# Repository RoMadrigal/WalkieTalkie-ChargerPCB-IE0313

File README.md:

# WalkieTalkie-ChargerPCB-IE0313

Repositorio para la tarea del curso IE0313 sobre el diseño de una PCB de una fuente de alimentación para un Walkie-Talkie. Contiene el circuito esquemático, el diseño de la PCB en KiCad y documentación sobre los componentes a utilizar, el procedimiento de diseño y otros detalles. 

Este repositorio y sus contenidos fueron diseñados durante el curso IE0313 durante el periodo II-2024 por los siguientes integrantes del equipo:

<div align="center">

|        **Integrantes**      | **Carné** | **Correo electrónico**|
|:---------------------------:|:---------:|:---------------------:|
|    Anthony Calvo García     |   C11433  |  anthonycalvo50@gmail.com |
|   Rodrigo Madrigal Montes   |   C24458  | rmadrigalmontes@gmail.com |

</div>

## Agradecimientos a PCBWay

Queremos expresar nuestros agradecimientos a **PCBWay** por su increíble apoyo en la fabricación de las PCBs para esta tarea. Desde el primer contacto hasta la recepción de las placas, la experiencia fue excelente. Las PCBs que recibimos superaron nuestras expectativas en términos de precisión y acabado. Cada detalle fue manejado con cuidado, asegurando un rendimiento óptimo y mostrando una calidad sobresaliente.

La comunicación fue clara y fluida, y el tiempo de entrega se cumplió en el plazo esperado. Recibimos las placas en perfectas condiciones, en un empaque seguro y listas para ensamblar. Además siempre estuvieron disponibles para responder preguntas y asegurarse de que todo saliera según lo planeado, lo cual nos brindó seguridad y apoyo durante todo el proceso de pedido.

### Resultado del ensamblaje

Soldar y ensamblar estas placas fue una experiencia cómoda y bastante agradable, ya que todas las medidas de las huellas que se escogieron para los componentes en la fase de diseño corresponden perfectamente en el producto terminado y los resultados finales son un testimonio del compromiso de **PCBWay** con la excelencia. Aquí se muestran fotografías de la PCB ensamblada y terminada:

|  |
|:--:|
| *Vista frontal de la PCB sin ensamblar* |

|  |
|:--:|
| *Vista trasera de la PCB sin ensamblar* |

Como se ve las placas se corresponden con lo esperado, y una vez se soldaron los componentes el resultado es el siguiente:

|  |
|:--:|
| *Vista frontal de la PCB ensamblada* |

|  |
|:--:|
| *Vista isométrica de la PCB ensamblada* |

|  |
|:--:|
|  |

Recomendamos sus servicios para cualquiera que busque fabricar PCBs con precisión y profesionalismo, visitando su sitio web en [pcbway.com](https://www.pcbway.com).

## Organización y contenido de los directorios 

Este repositorio contiene dos directorios principales, cuyos contenidos son:

- `kicad_project`: Contiene los archivos de diseño y configuarción del proyecto
    - `CargadorWalkieTalkie.kicad_pcb`
    - `CargadorWalkieTalkie.kicad_pro`
    - `CargadorWalkieTalkie.kicad_sch`

- `outputs`: Contiene todos los archivos de salida de *KiCad*

Si se desea utilizar este diseño y manufacturarlo por medio de un fabricante se debe comprimir los archivos incluidos en la carpeta `outputs` en un archivo `.zip` y este se puede cargar en la página del fabricante para ordenar la fabricación de la PCB. 

## Circuito base

El circuito del que partimos para diseñar la PCB es el que se diseñó en la **Tarea 3**:

<div align="center">

|  |
|:--:|
| *Circuto de la fuente de alimentación* |

</div>

Para este ciruito se tiene el siguiente listado de componentes:

<div align="center">

|     Componente     | Especificación |
|:------------------:|:--------------:|
|    Transformador   |      20:1      |
| Diodo rectificador |     1N4007     |
|      Capacitor     |     1.1 mF     |
|     Resistencia    |      6 Ω       |
|     Diodo Zener    |     1N5338B    |
|      Fusible 1     |     400 mA     |
|      Fusible 2     |     200 mA     |

</div>

## Diseño del esquemático 

Primero para el diseño del esquemático de la PCB se seleccionó la opción *Schematic Editor* en *KiCad*, posteriormente se siguió la metodología de pasos descrita en la página de [Arcos-Lab Wiki](https://wiki.arcoslab.org/en/tutorials/kicad/example), a lo cual primero se definieron el el título, fecha y revisión del proyecto. 

Posteriormente se procedió a agregar los símbolos de cada componente a utilizar en el esquemático, acomodarlos y realizar las conexiones, a lo cual se obtuvo lo siguiente:

<div align="center">

|  |
|:--:|
| *Diseño del esquemático* |

</div>

Aquí hay algunas elecciones que es importante mencionar son:

### Transformador

Se realizó una investigación sobre diseños de circuitos en el mismo programa que eran similares a este y se encontró que en base a las recomendaciones y experiencias de estos usuarios determinamos que era mejor dejar el transformador fuera de la PCB ya que consumen mucho más espacio y es más seguro conectarlo como un componente externo, por lo cual para este diseño consideramos que la salida del transformador se conecta en la terminal `J1`. 

### Elección de huellas y componentes

Por otro lado en cuanto a las huellas de los componentes por ejemplo para los diodos, tanto para los `1n4007` y el `1n5338B` se utilizo la huella que ya venía asignada por defecto en el programa; y aplicamos lo mismo para la resistencia y las terminales. Ahora bien en cuanto al capacitor se realizó la busqueda de varios capacitores disponibles en el mercado para poder determinar las dimensiones a utilizar del mismo. 

Nos terminamos decantando por los modelos de capacitor del fabricante **Vishay** de una capacitancia de 1200 μF que es lo más cercano al valor teórico que definimos en el circuito. Y se utilizaron las medidas presentes en el [Datasheet 135D, 135J, 135L](https://www.vishay.com/docs/40024/135d-135j-135l.pdf) y se asignaron a la huella en el esquemático. Y además se agregó el *Datasheet* del mismo en la tabla de componentes en el programa para poder acceder rápidamente al mismo sin necesidad de salir del programa y buscarlo. 

Después se procedió a colocar las etiquetas a los nodos `Vs` y `gnd` para los nodos de alimentación y tierra, y se colocaron los símbolos de `PWR_FLAG` para indicar a *KiCad* que es por medio de estos nodos que se alimentará el circuito. 

Y una vez realizados todos los pasos anteriores se procedió a seleccionar la opción *Perform electrical rules check* para verificar que no haya conexiones inválidas o algún error en alguna configuración del circuito a lo cual obtuvimos una salida sin errores. 

## Diseño de la PCB

Primero se realizó la configuración previa en el editor de PCB, donde definimos que la placa tendría dos capas y se definieron el el título, fecha y revisión del proyecto en esta página. Posteriormente se utilizó la opción *Update PCB with schematic changes* para poder importar los modelos del esquemático a la página del editor de PCB.

Luego de esto se procedió a acomodar los componente en el editor tomando en cuenta la configuarción que menos espacio requiera y sea fácil de reconocer cada componente. Se realizaron las conexiones de los componentes, entre las capas **F. Cu** y **B. Cu** y se asignó que en la capa **F. Cu** se conectaría el nodo `gnd` y la capa **B. Cu** va ligada a `Vs`. Por último se procedió a hacer el relleno de cada capa dentro del recuadro definido de la PCB que definimos y se corrieron las pruebas dentro del programa para asegurar que no haya errores, a lo cual se obtuvieron los siguientes resultados:

<div align="center">

|  |
|:--:|
| *Vista de la PCB con ambas capas superpuestas* |

</div>

Y viendo las conexiones de cada capa por separado se tiene los siguiente:

<div align="center">

|  |
|:--:|
| *Capa **F. Cu** de la PCB* |

</div>

<div align="center">

|  |
|:--:|
| *Capa **B. Cu** de la PCB* |

</div>

### Consideraciones adicionales

Por cuestiones de tiempo por el momento para este diseño no se tomó en cuenta la configuración del tamaño de las pistas de conexión en la PCB, pero esto queda pendiente como una futura mejora para el adecuado funcionamiento y como protección del circuito. Además tampoco tomamos en cuenta los fusibles en la placa por el mismo motivo y queda igualmente pendiente como mejora al diseño. 

Antes de terminar el diseño agregamos los nombre de los integrantes y de la placa (`WT-Charger V1`) en la parte trasera de la PCB haciendo uso de la capa **B. Silkscreen**, que como observación importante notamos que todo lo que se agregue en esta capa ya sea texto o un logo desde el editor debe verse en espejo ya que el editor mira la placa desde el frente de la misma. Agregando este cambio se consiguió lo siguente:

<div align="center">

|  |
|:--:|
| *Nombre de la placa y los integrantes en la parte trasera de la PCB* |

</div>

## Resultados finales

Como muestra de los resultados finales de este diseño se utilzó el visor 3D de *KiCad* para poder visualizar mejor la PCB, a lo cual se muestran los resultados finales en las siguientes imágenes:

<div align="center">

|  |
|:--:|
| *Vista frontal de la PCB* |

</div>

<div align="center">

|  |
|:--:|
| *Vista trasera de la PCB* |

</div>

<div align="center">

|  |
|:--:|
| *Vista isométrica de la PCB* |

</div>

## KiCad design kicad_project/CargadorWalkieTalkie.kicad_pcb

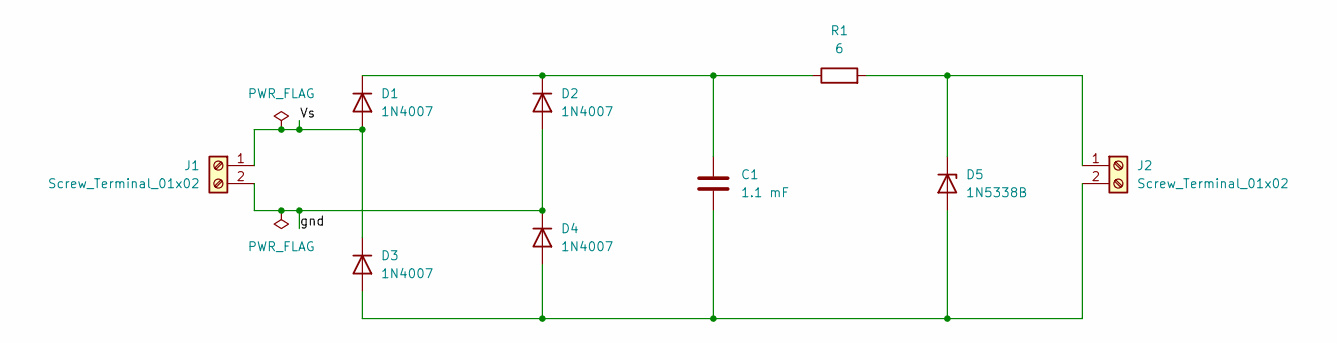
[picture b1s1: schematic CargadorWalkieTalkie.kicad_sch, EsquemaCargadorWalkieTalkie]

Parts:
C1: 1.1 mF; CP_Axial_L18.0mm_D6.5mm_P25.00mm_Horizontal
D1, D2, D3, D4: 1N4007; D_DO-41_SOD81_P10.16mm_Horizontal
D5: 1N5338B; D_DO-201_P15.24mm_Horizontal
J1, J2: Screw_Terminal_01x02; TerminalBlock_bornier-2_P5.08mm
R1: 6; R_Axial_DIN0204_L3.6mm_D1.6mm_P5.08mm_Horizontal

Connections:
/Vs: D1.2 (A), D3.1 (K), J1.1
/gnd: D2.2 (A), D4.1 (K), J1.2
unnamed: C1.1, D1.1 (K), D2.1 (K), R1.1
unnamed: C1.2, D3.2 (A), D4.2 (A), D5.2 (A), J2.2
unnamed: D5.1 (K), J2.1, R1.2

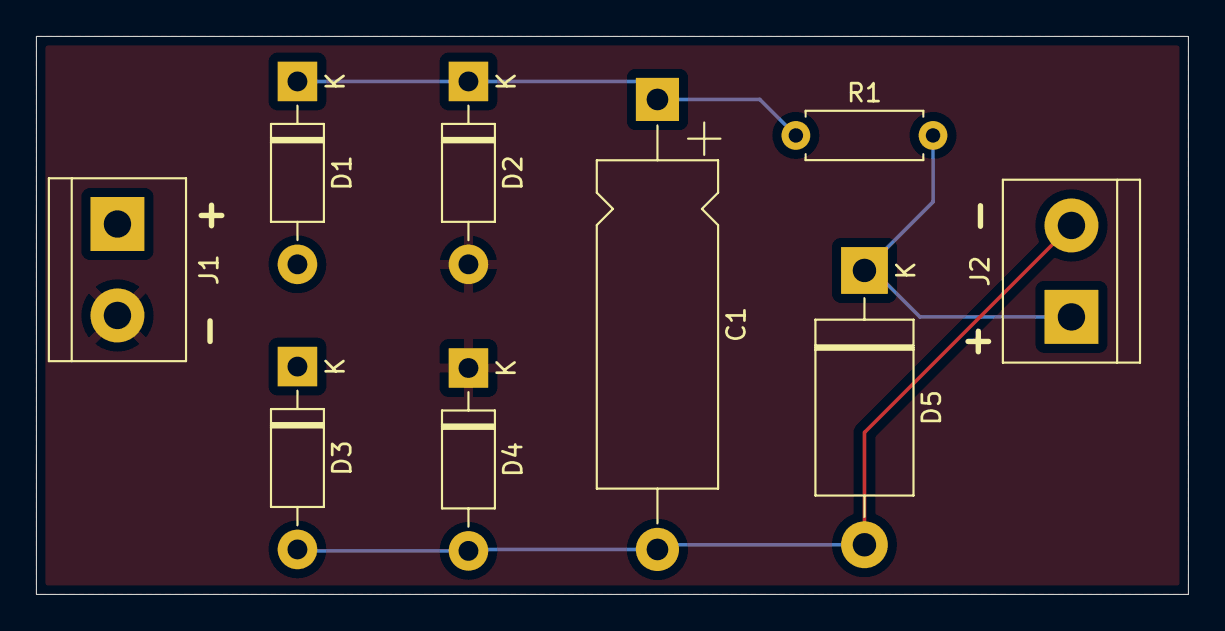
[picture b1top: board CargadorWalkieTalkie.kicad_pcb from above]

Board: 2 copper layers, 64.0 x 31.0 mm, 9 parts (0 on the bottom side), 5 nets.

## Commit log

2024-11-24 Agregando directorios y archivos adicionales en el .gitignore
2024-11-24 Agregando los archivos del proyecto de la PCB
2024-11-24 Ajustando formato en el README.md
2024-11-24 Eliminando archivos de la PCB de la rama documentation
2024-11-25 Agregando las capas y enrutamiento en las capas de la PCB
2024-11-25 Agregando nombres de los integrantes y del proyecto en la PCB
2024-11-25 Agregando los archivos de fabricacion de la PCB
2024-12-02 Agregando enlace del datasheet del capacitor en el esquematico
2024-12-02 Agregando integrantes y especificaciones del circuito base
2024-12-02 Se agrega la imagen del circuito base del diseño
2024-12-03 Agregando especificaciones del esquematico en el README.md
2024-12-03 Agregando fase de eleccion de componentes y huellas en el README.md
2024-12-03 Agregando seccion de consideraciones adicionales en el README.md
2024-12-03 Agregando seccion de resultados finales en el README.md
2024-12-03 Agregando seccion de organizacion de directorios al README.md
2025-01-21 Agregando apartado de agradecimentos a PCBWay en el README.md
2025-09-26 Agregando imagenes actualizadas de la PCB en el README.md
2025-09-26 Actualizando archivos de fabricacion con los ultimos cambios
2025-09-26 Agregando modelo 3D de los terminales y eliminando rutas redundantes
